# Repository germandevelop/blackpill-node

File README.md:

# blackpill-node
## Build firmware
### Release ###
```
mkdir ./build
cd ./build
cmake ..
make silver
```
### Debug ###
```
mkdir ./build
cd ./build
cmake -DCMAKE_BUILD_TYPE=Debug ..
make silver
```
## Flash
### Flash firmware ###
```
make flash
```
### Erase firmware ###
```
make erase
```
## Build tests
### Build ###
```
mkdir ./build
cd ./build
cmake -DCMAKE_BUILD_TYPE=Debug -DBUILD_TESTS=ON ..
make tests
```
### Run ###
```
make test
```

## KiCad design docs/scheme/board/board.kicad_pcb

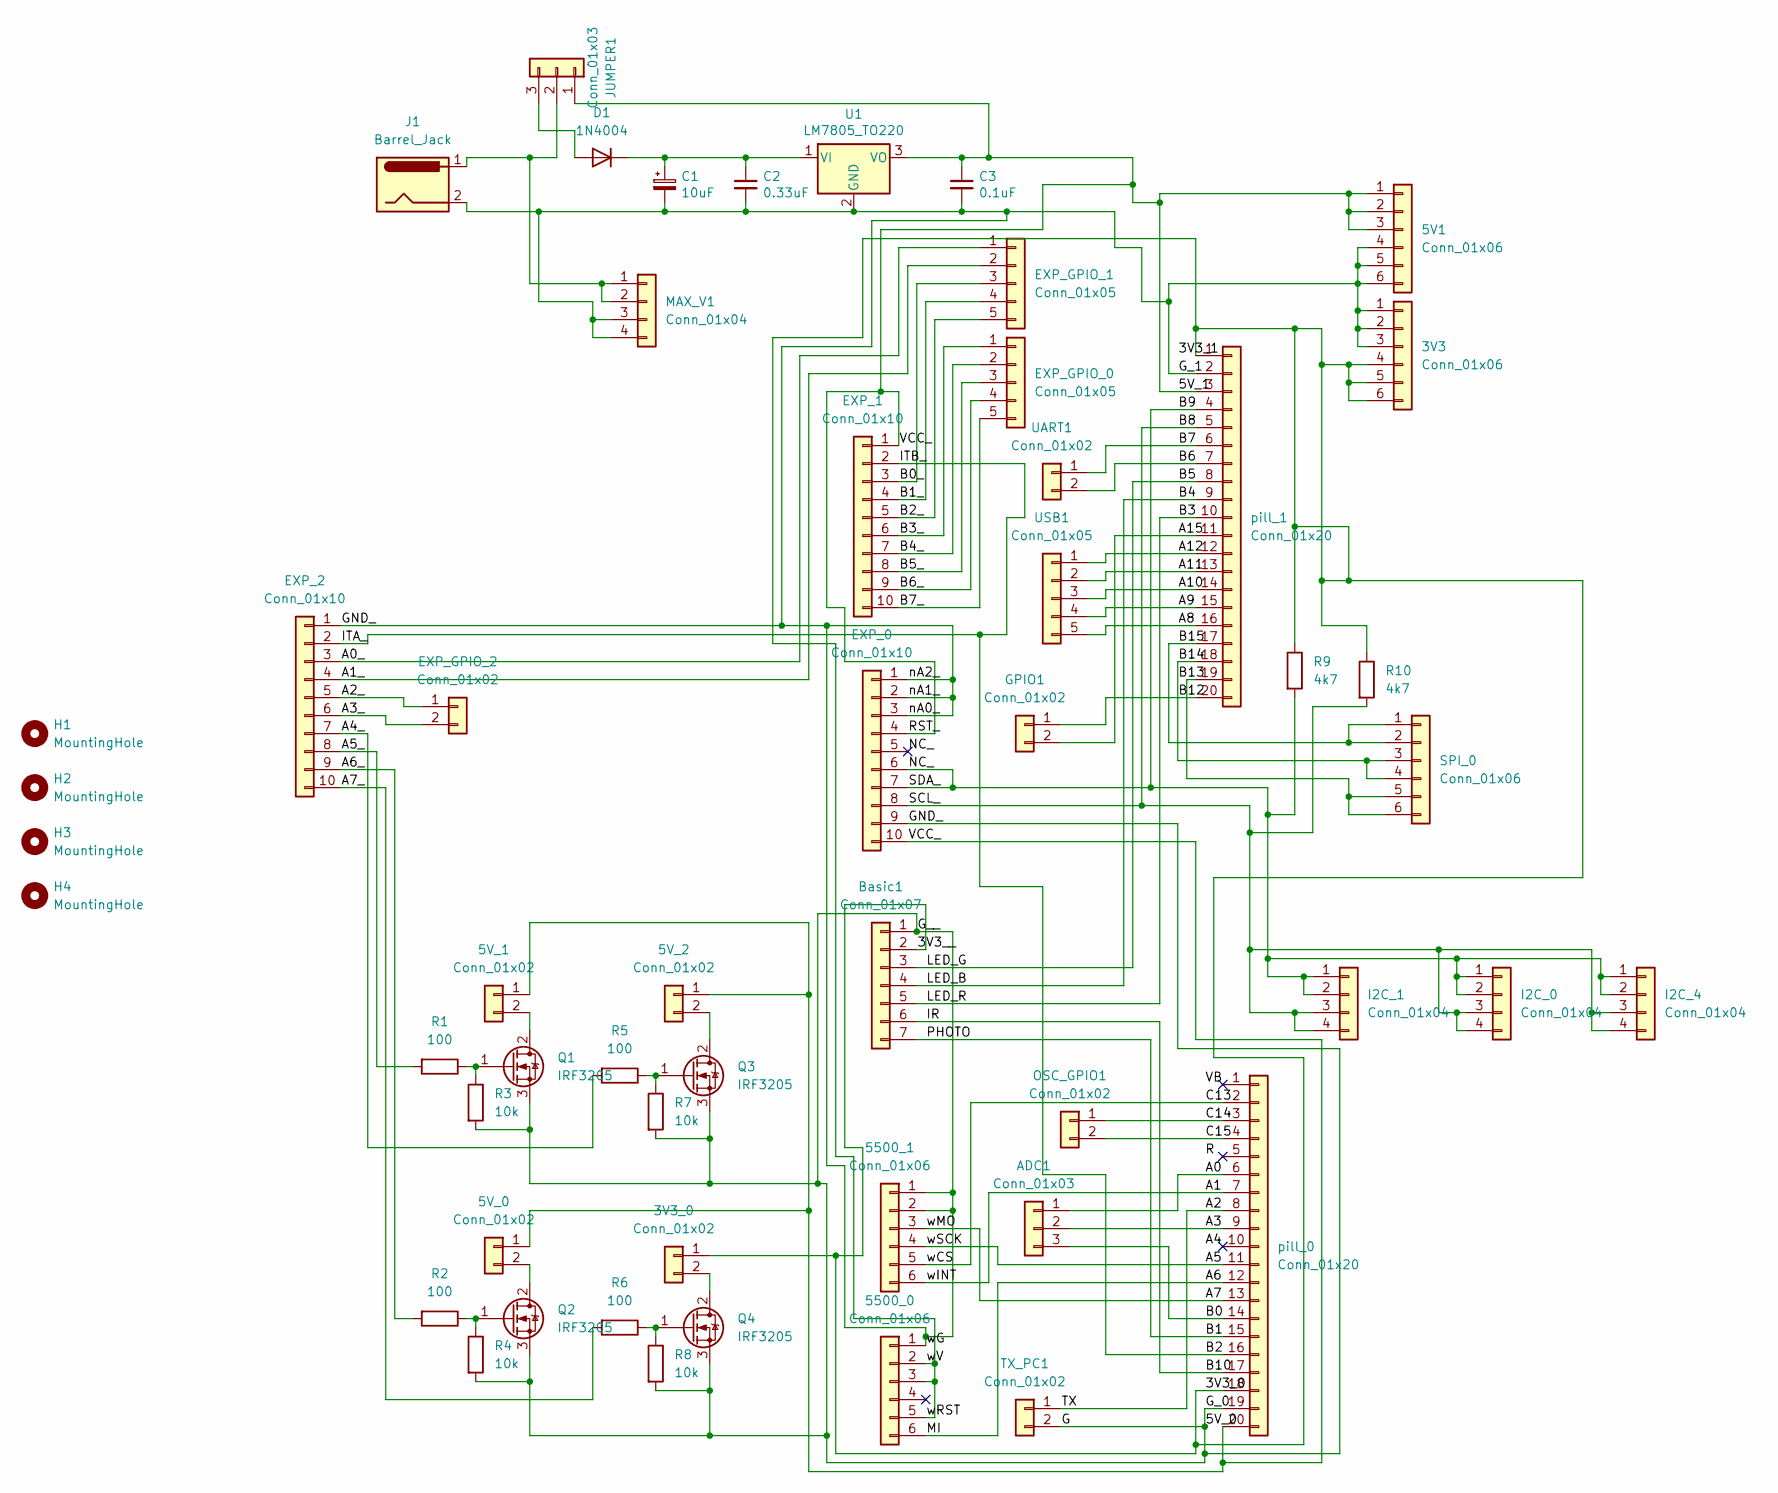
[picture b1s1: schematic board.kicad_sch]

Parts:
3V3, 5V1, 5500_0, 5500_1: Conn_01x06; PinHeader_1x06_P2.54mm_Vertical
3V3_0, 5V_0, 5V_1, 5V_2: Conn_01x02; PinHeader_1x02_P2.54mm_Vertical
ADC1: Conn_01x03; PinHeader_1x03_P2.54mm_Vertical
Basic1: Conn_01x07; PinHeader_1x07_P2.54mm_Vertical
C1: 10uF; CP_Radial_Tantal_D4.5mm_P2.50mm
C2: 0.33uF; CP_Radial_Tantal_D4.5mm_P5.00mm
C3: 0.1uF; CP_Radial_Tantal_D4.5mm_P5.00mm
D1: 1N4004; D_DO-41_SOD81_P10.16mm_Horizontal
EXP_0, EXP_1, EXP_2: Conn_01x10; PinHeader_1x10_P2.54mm_Vertical
EXP_GPIO_0, EXP_GPIO_1: Conn_01x05; PinHeader_1x05_P2.54mm_Vertical
EXP_GPIO_2: Conn_01x02; PinHeader_1x02_P2.54mm_Vertical
GPIO1: Conn_01x02; PinHeader_1x02_P2.54mm_Vertical
H1, H2, H3, H4: MountingHole; MountingHole_2.5mm_Pad
I2C_0, I2C_1, I2C_4: Conn_01x04; PinHeader_1x04_P2.54mm_Vertical
J1: Barrel_Jack; BarrelJack_Horizontal
JUMPER1: Conn_01x03; PinHeader_1x03_P2.54mm_Vertical
MAX_V1: Conn_01x04; PinHeader_1x04_P2.54mm_Vertical
OSC_GPIO1: Conn_01x02; PinHeader_1x02_P2.54mm_Vertical
Q1, Q2, Q3, Q4: IRF3205; TO-220-3_Vertical
R1, R2, R5, R6: 100; R_Axial_DIN0207_L6.3mm_D2.5mm_P10.16mm_Horizontal
R3, R4, R7, R8: 10k; R_Axial_DIN0207_L6.3mm_D2.5mm_P10.16mm_Horizontal
R9, R10: 4k7; R_Axial_DIN0207_L6.3mm_D2.5mm_P10.16mm_Horizontal
SPI_0: Conn_01x06; PinHeader_1x06_P2.54mm_Vertical
TX_PC1: Conn_01x02; PinHeader_1x02_P2.54mm_Vertical
U1: LM7805_TO220; TO-220-3_Vertical
UART1: Conn_01x02; PinHeader_1x02_P2.54mm_Vertical
USB1: Conn_01x05; PinHeader_1x05_P2.54mm_Vertical
pill_0, pill_1: Conn_01x20; PinHeader_1x20_P2.54mm_Vertical

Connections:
/3V3_0: 3V3.4, 3V3.5, 3V3.6, 3V3_0.1, 5500_0.2, 5500_0.3, 5500_0.5, Basic1.2, R9.1, R10.1, pill_0.18, pill_1.1
/5V_0: 3V3.1, 3V3.2, 3V3.3, 5V1.4, 5V1.5, 5V1.6, 5500_0.1, 5500_1.1, 5500_1.2, Basic1.1, C1.2, C2.2, C3.2, EXP_0.1, EXP_0.2, EXP_0.3, EXP_0.9, EXP_2.1, J1.2, MAX_V1.3, MAX_V1.4, Q1.3 (S), Q2.3 (S), Q3.3 (S), Q4.3 (S), R3.2, R4.2, R7.2, R8.2, TX_PC1.2, U1.2 (GND), pill_0.19, pill_1.2
/5V_1: 5V1.1, 5V1.2, 5V1.3, 5V_0.1, 5V_1.1, 5V_2.1, C3.1, EXP_0.4, EXP_0.10, EXP_1.1, JUMPER1.1, U1.3 (VO), pill_0.20, pill_1.3
/A0: ADC1.1, pill_0.6
/A0_: EXP_2.3, EXP_GPIO_1.1
/A1: 5500_1.6, pill_0.7
/A1_: EXP_2.4, EXP_GPIO_1.2
/A2: TX_PC1.1, pill_0.8
/A2_: EXP_2.5, EXP_GPIO_2.1
/A3: ADC1.2, pill_0.9
/A3_: EXP_2.6, EXP_GPIO_2.2
/A4_: EXP_2.7, R5.2
/A5: 5500_1.4, pill_0.11
/A5_: EXP_2.8, R1.2
/A6: 5500_0.6, pill_0.12
/A6_: EXP_2.9, R2.2
/A7: 5500_1.3, pill_0.13
/A7_: EXP_2.10, R6.2
/A8: USB1.5, pill_1.16
/A9: USB1.4, pill_1.15
/A10: USB1.3, pill_1.14
/A11: USB1.2, pill_1.13
/A12: USB1.1, pill_1.12
/A15: GPIO1.2, pill_1.11
/B0: ADC1.3, pill_0.14
/B0_: EXP_1.3, EXP_GPIO_1.3
/B1: Basic1.7, pill_0.15
/B1_: EXP_1.4, EXP_GPIO_1.4
/B2: EXP_1.2, EXP_2.2, pill_0.16
/B2_: EXP_1.5, EXP_GPIO_1.5
/B3: Basic1.5, pill_1.10
/B3_: EXP_1.6, EXP_GPIO_0.1
/B4: Basic1.4, pill_1.9
/B4_: EXP_1.7, EXP_GPIO_0.2
/B5: Basic1.3, pill_1.8
/B5_: EXP_1.8, EXP_GPIO_0.3
/B6: UART1.2, pill_1.7
/B6_: EXP_1.9, EXP_GPIO_0.4
/B7: UART1.1, pill_1.6
/B7_: EXP_1.10, EXP_GPIO_0.5
/B8: EXP_0.8, I2C_0.3, I2C_0.4, I2C_1.3, I2C_1.4, I2C_4.3, I2C_4.4, R10.2, pill_1.5
/B9: EXP_0.5, EXP_0.6, EXP_0.7, I2C_0.1, I2C_0.2, I2C_1.1, I2C_1.2, I2C_4.1, I2C_4.2, R9.2, pill_1.4
/B10: Basic1.6, pill_0.17
/B15: SPI_0.1, SPI_0.2, pill_1.17
/C13: 5500_1.5, pill_0.2
/C14: OSC_GPIO1.1, pill_0.3
/C15: OSC_GPIO1.2, pill_0.4
unnamed: 3V3_0.2, Q4.2 (D)
unnamed: 5V_0.2, Q2.2 (D)
unnamed: 5V_1.2, Q1.2 (D)
unnamed: 5V_2.2, Q3.2 (D)
unnamed: C1.1, C2.1, D1.1 (K), U1.1 (VI)
unnamed: D1.2 (A), JUMPER1.3
unnamed: J1.1, JUMPER1.2, MAX_V1.1, MAX_V1.2
unnamed: Q1.1 (G), R1.1, R3.1
unnamed: Q2.1 (G), R2.1, R4.1
unnamed: Q3.1 (G), R5.1, R7.1
unnamed: Q4.1 (G), R6.1, R8.1
unnamed: SPI_0.5, SPI_0.6, pill_1.19

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
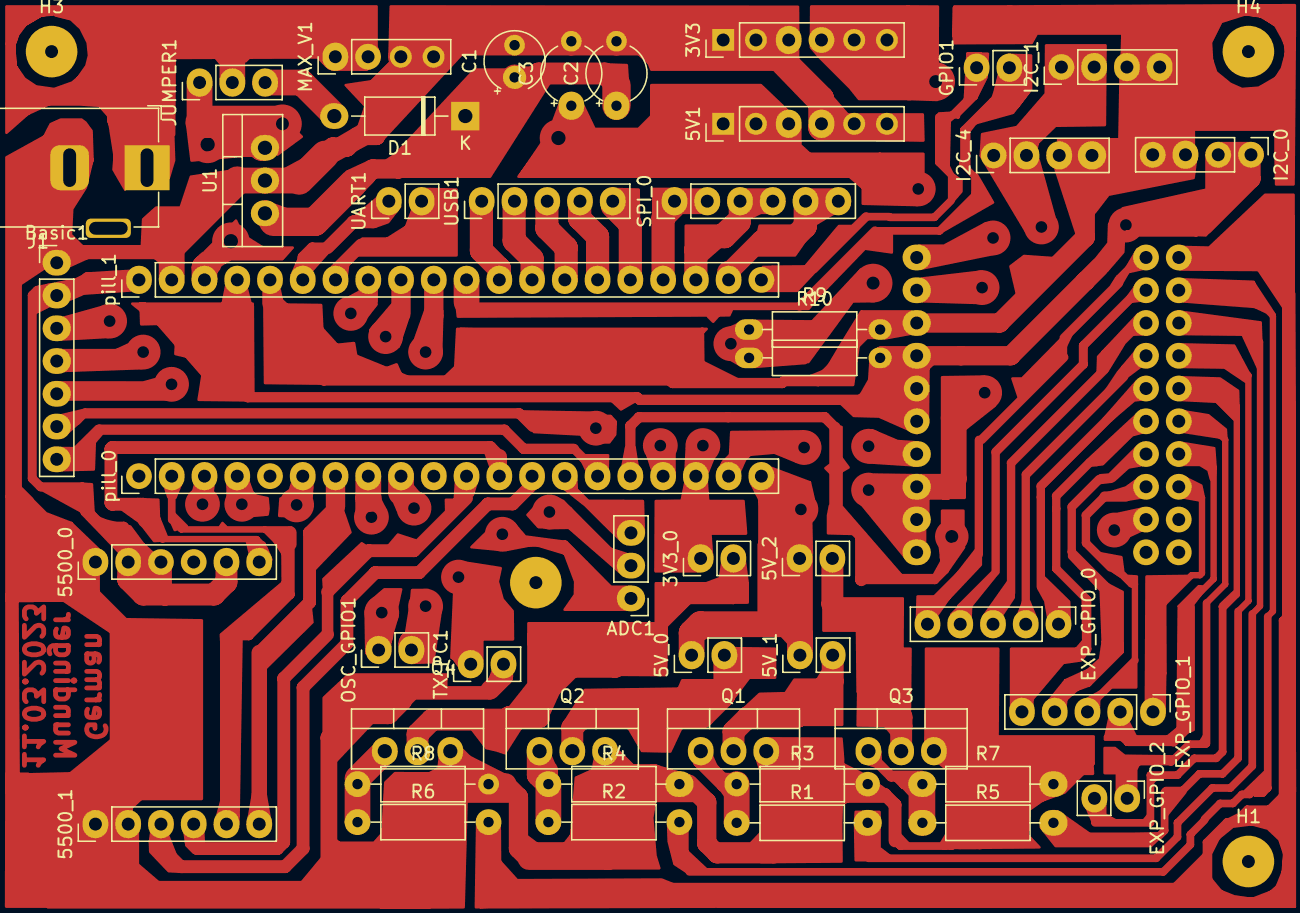
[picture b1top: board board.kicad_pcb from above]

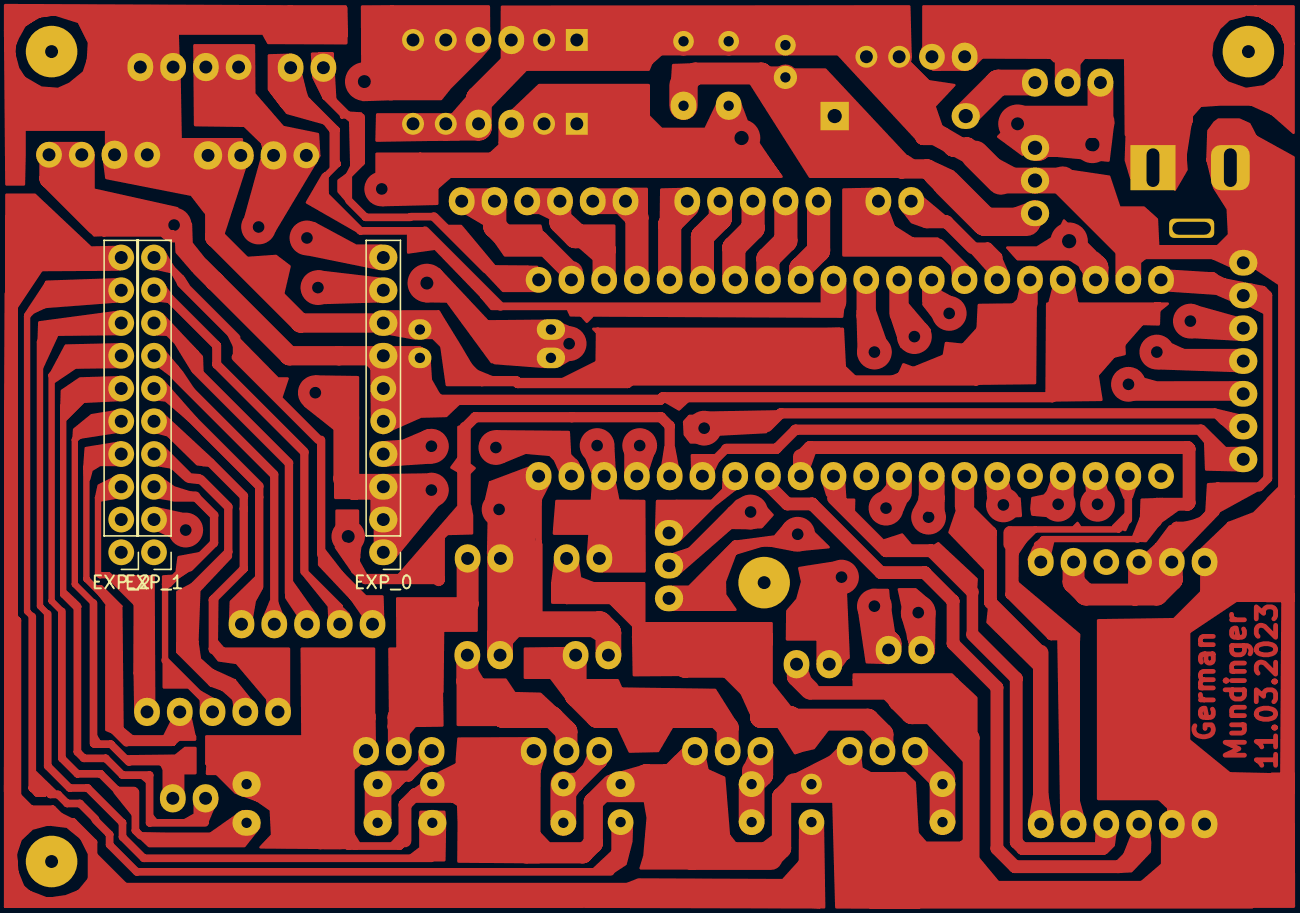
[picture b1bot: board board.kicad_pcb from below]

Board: 2 copper layers, 52 parts (3 on the bottom side), 61 nets.

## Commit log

2024-02-03 Initial
2024-02-04 Fix something
2024-02-08 Add simple bootloader
2024-02-09 Fix sysclock
2024-02-09 Add gold
2024-02-22 Add T01 node
2024-02-27 Add FreeBSD support
2024-02-29 Update node
2024-02-29 Update tests
2024-03-02 Complete tests
2024-03-02 Init docs
2024-03-03 Update docs
2024-03-05 Fix photoresist
2024-03-05 Refactor
2024-03-18 Add node type
2024-03-18 Update FreeBSD support
2024-03-18 Fix FreeBSD support
2024-04-03 Add B02 node
2024-04-04 Extract storage
2024-04-05 Add initial factory
2024-04-06 Add initial B02 board
2024-04-07 Complete board B02
2024-04-11 Improve boards
2024-04-12 add i2c lock
2024-04-12 Backup
2024-04-20 Complete bootloader
2024-05-18 Complete T01
2024-05-20 Complete B02 node
2024-06-04 Improve pre-release
2024-06-05 Pre release 0.1.0
